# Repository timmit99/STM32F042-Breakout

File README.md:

# STM32F042 Breakout #

[Interactive bom](http://htmlpreview.github.io/?https://github.com/timmit99/STM32F042-Breakout/blob/main/ibom.html)

## The board has: ##
 - STM32F042F6P6 MCU with internal oscillator
 - USB port
 - Reset button
 - All GPIO pins broken out
 - Silkscreen (kinda)
 - Power and PB1 LED

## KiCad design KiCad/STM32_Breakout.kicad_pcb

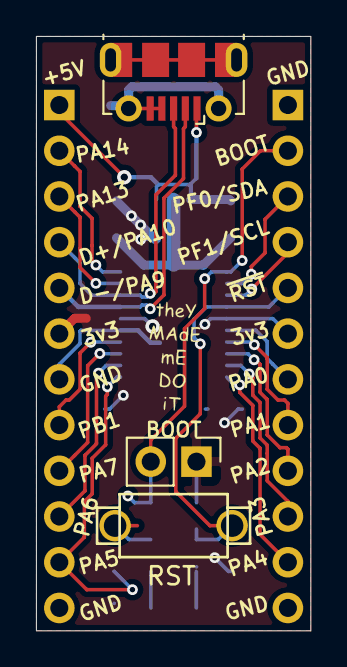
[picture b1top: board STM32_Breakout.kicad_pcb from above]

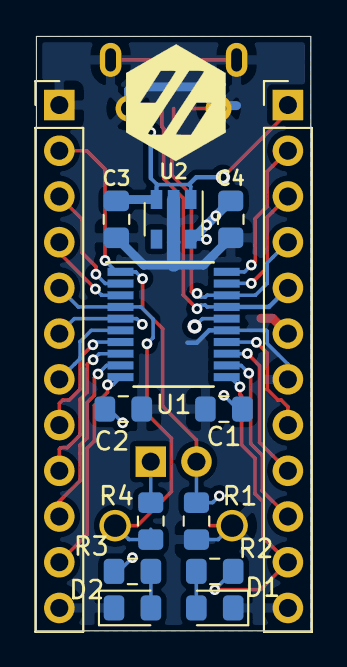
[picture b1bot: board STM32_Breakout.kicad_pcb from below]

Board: 2 copper layers, 15.2 x 33.0 mm, 17 parts (14 on the bottom side), 22 nets.

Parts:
C1, C2, C3, C4: 4.7uF; C_0805_2012Metric_Pad1.15x1.40mm_HandSolder
D1, D2: LED; LED_0805_2012Metric_Pad1.15x1.40mm_HandSolder
J1: USB_B_Micro; Molex-105017-0001-USBMicroB
J2: Conn_01x02; PinHeader_1x02_P2.54mm_Vertical
J3, J4: Conn_01x12; PinHeader_1x12_P2.54mm_Vertical
R1, R4: 10K; R_0805_2012Metric_Pad1.15x1.40mm_HandSolder
R2, R3: 1K; R_0805_2012Metric_Pad1.15x1.40mm_HandSolder
RST: SW_SPST; 2PinTactileButton
U1: STM32F042F6Px; TSSOP-20_4.4x6.5mm_P0.65mm
U2: AP2127K-3.3; SOT-23-5

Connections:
3v3: C1.1, C2.1, C4.1, J2.1, J3.6, J4.6, R3.1, R4.1, U1.5, U1.16, U2.5
BOOT0: J2.2, J3.2, R1.1, U1.1
D+: J1.3, J4.4, U1.18
D-: J1.2, J4.5, U1.17
GND: C1.2, C2.2, C3.2, C4.2, D1.1, D2.1, J1.4, J1.5, J1.6, J3.1, J3.12, J4.7, J4.12, R1.2, RST.1, U1.15, U2.2
unnamed: D1.2, R2.2
unnamed: D2.2, R3.2
PA0: J3.7, U1.6
PA1: J3.8, U1.7
PA2: J3.9, U1.8
PA3: J3.10, U1.9
PA4: J3.11, U1.10
PA5: J4.11, R2.1, U1.11
PA6: J4.10, U1.12
PA7: J4.9, U1.13
PA13: J4.3, U1.19
PA14: J4.2, U1.20
PB1: J4.8, U1.14
PF0-SDA: J3.3, U1.2
PF1-SCL: J3.4, U1.3
VBUS: C3.1, J1.1, J4.1, U2.1, U2.3
~RESET: J3.5, R4.2, RST.2, U1.4

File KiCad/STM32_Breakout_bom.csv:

Reference, Value, Footprint, Datasheet
"U1","STM32F042F6Px","Package_SO:TSSOP-20_4.4x6.5mm_P0.65mm","http://www.st.com/st-web-ui/static/active/en/resource/techni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"
"J1","USB_B_Micro","STM32_Breakout:Molex-105017-0001-USBMicroB","~"
"U2","AP2127K-3.3","Package_TO_SOT_SMD:SOT-23-5","https://www.diodes.com/assets/Datasheets/AP2127.pdf"
"C3","4.7uF","Capacitor_SMD:C_0805_2012Metric_Pad1.15x1.40mm_HandSolder","~"
"C4","4.7uF","Capacitor_SMD:C_0805_2012Metric_Pad1.15x1.40mm_HandSolder","~"
"C1","4.7uF","Capacitor_SMD:C_0805_2012Metric_Pad1.15x1.40mm_HandSolder","~"
"C2","4.7uF","Capacitor_SMD:C_0805_2012Metric_Pad1.15x1.40mm_HandSolder","~"
"RST1","SW_SPST","STM32_Breakout:2PinTactileButton","~"
"R4","10K","Resistor_SMD:R_0805_2012Metric_Pad1.15x1.40mm_HandSolder","~"
"J2","Conn_01x02","Connector_PinHeader_2.54mm:PinHeader_1x02_P2.54mm_Vertical","~"
"R1","10K","Resistor_SMD:R_0805_2012Metric_Pad1.15x1.40mm_HandSolder","~"
"D2","LED","LED_SMD:LED_0805_2012Metric_Pad1.15x1.40mm_HandSolder","~"
"R3","1K","Resistor_SMD:R_0805_2012Metric_Pad1.15x1.40mm_HandSolder","~"
"D1","LED","LED_SMD:LED_0805_2012Metric_Pad1.15x1.40mm_HandSolder","~"
"R2","1K","Resistor_SMD:R_0805_2012Metric_Pad1.15x1.40mm_HandSolder","~"
"J4","Conn_01x12","Connector_PinHeader_2.54mm:PinHeader_1x12_P2.54mm_Vertical","~"
"J3","Conn_01x12","Connector_PinHeader_2.54mm:PinHeader_1x12_P2.54mm_Vertical","~"

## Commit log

2020-12-19 Initial release
    Initial release of STM32F042 dev board.
    Has VERY limited (i.e. crappy) silkscreen so use at own risk.
2020-12-19 Addition of images and Readme changes
2020-12-19 Update for additional... something
    Added silkscreen labels, moved SMD parts to bottom,
2020-12-19 Gerber addition
2020-12-19 update iBom
2020-12-19 move iBom to correct location
2021-03-17 add ignore
2021-03-17 Clean up ignored files
2021-03-17 save unsaved changes
2021-03-17 Update pin
2021-03-18 Patch 002 (#1)
    * add ignore
    * Clean up ignored files
    * save unsaved changes
    * Update pin
